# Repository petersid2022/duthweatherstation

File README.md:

# duthweatherstation

This repo contains a proposed implementation of an Integrated Automatic Weather Station, centered around the FireBeetle 2 ESP32-E microcontroller, that's based on the ESP-WROOM-32E, chosen for its ultra-low power consumption, on-board charging circuit and compatibility with a wide range of sensors. The sensor array includes a DHT11 for humidity, a BMP180 for temperature and barometric pressure, and an MQ135 for air quality monitoring.

Included in this repo:
* The ESP32 firmware
* The Go microservice that handles the data stream from the ESP32 and various SQL transactions with the MySQL database
* Our Go/TEMPL frontend app
* The final board schematic, designed using KiCad
* Various 3D renderings of the PCB generated using KiCad
* The paper that describes in detail our implementation

~~You can view the live production app on: https://duthweatherstation.azurewebsites.net/~~

## License
This project is licensed under the MIT License.

(The MIT License)
Copyright (c) 2024 Peter Sideris petersid2022@gmail.com
Permission is hereby granted, free of charge, to any person obtaining a copy of this software and associated documentation files (the 'Software'), to deal in the Software without restriction, including without limitation the rights to use, copy, modify, merge, publish, distribute, sublicense, and/or sell copies of the Software, and to permit persons to whom the Software is furnished to do so, subject to the following conditions:
The above copyright notice and this permission notice shall be included in all copies or substantial portions of the Software.
THE SOFTWARE IS PROVIDED 'AS IS', WITHOUT WARRANTY OF ANY KIND, EXPRESS OR IMPLIED, INCLUDING BUT NOT LIMITED TO THE WARRANTIES OF MERCHANTABILITY, FITNESS FOR A PARTICULAR PURPOSE AND NONINFRINGEMENT. IN NO EVENT SHALL THE AUTHORS OR COPYRIGHT HOLDERS BE LIABLE FOR ANY CLAIM, DAMAGES OR OTHER LIABILITY, WHETHER IN AN ACTION OF CONTRACT, TORT OR OTHERWISE, ARISING FROM, OUT OF OR IN CONNECTION WITH THE SOFTWARE OR THE USE OR OTHER DEALINGS IN THE SOFTWARE.

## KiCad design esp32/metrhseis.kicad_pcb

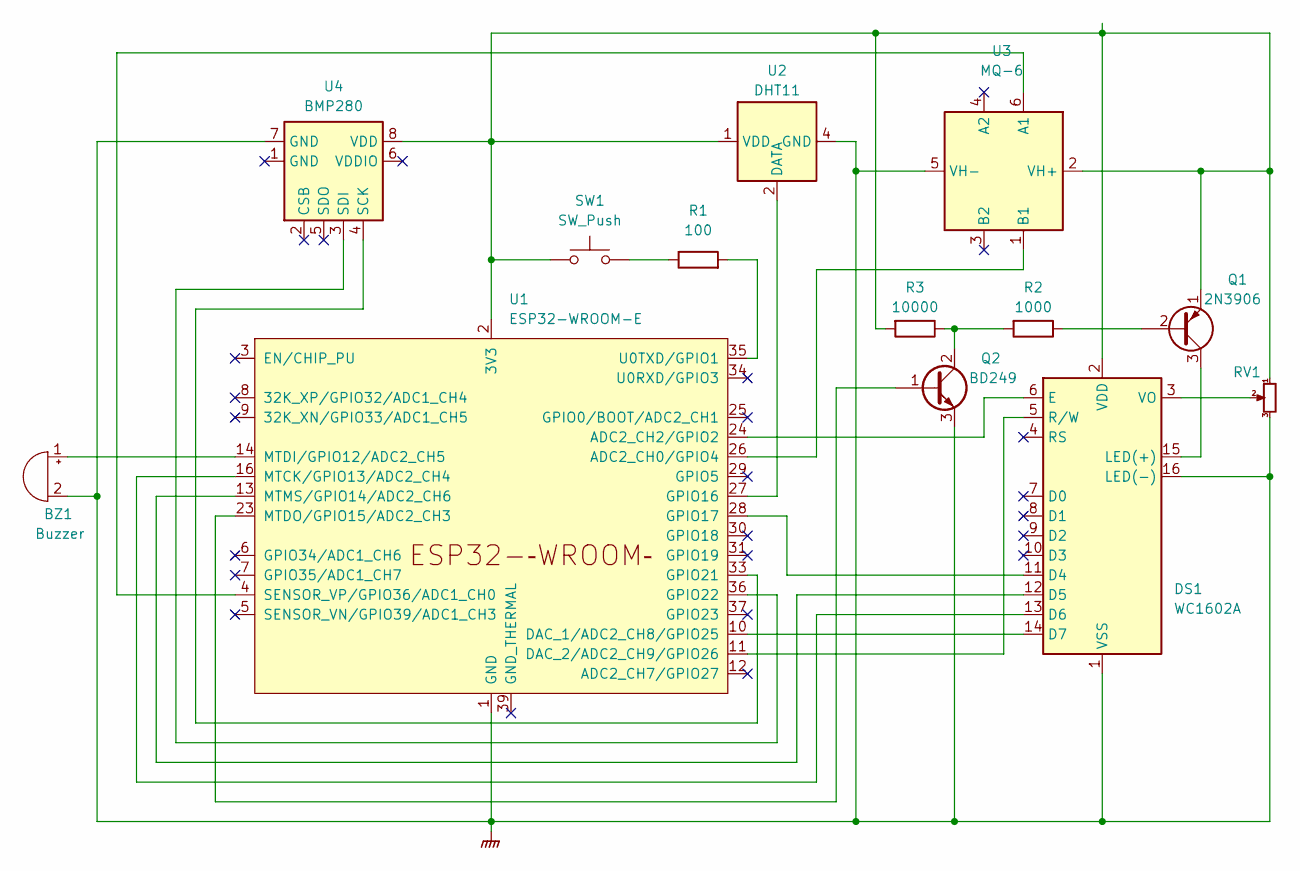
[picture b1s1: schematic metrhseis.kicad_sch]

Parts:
BZ1: Buzzer; Buzzer_12x9.5RM7.6
DS1: WC1602A
Q1: 2N3906; TO-92_Inline
Q2: BD249; SOT-1123
R1: 100; R_0603_1608Metric
R2: 1000; R_0603_1608Metric
R3: 10000; R_0603_1608Metric
RV1: R_Potentiometer_Small; Potentiometer_ACP_CA6-VSMD_Vertical
SW1: SW_Push; SW_PUSH_6mm
U1: ESP32-WROOM-E; ESP32-WROOM-32E
U2: DHT11; Aosong_DHT11_5.5x12.0_P2.54mm
U3: MQ-6
U4: BMP280; Bosch_LGA-8_2x2.5mm_P0.65mm_ClockwisePinNumbering

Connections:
GNDPWR: BZ1.2 (-), DS1.1 (VSS), DS1.16 (LED(-)), Q2.3 (E), RV1.3, U1.1 (GND), U1.15 (GND), U1.38 (GND), U2.4 (GND), U3.5 (VH-), U4.7 (GND)
unnamed: BZ1.1 (+), U1.14 (MTDI/GPIO12/ADC2_CH5)
unnamed: DS1.11 (D4), U1.28 (GPIO17)
unnamed: DS1.12 (D5), U1.13 (MTMS/GPIO14/ADC2_CH6)
unnamed: DS1.13 (D6), U1.16 (MTCK/GPIO13/ADC2_CH4)
unnamed: DS1.14 (D7), U1.10 (DAC_1/ADC2_CH8/GPIO25)
unnamed: DS1.6 (E), U1.24 (ADC2_CH2/GPIO2)
unnamed: DS1.15 (LED(+)), Q1.3 (C)
unnamed: DS1.5 (R/W), U1.11 (DAC_2/ADC2_CH9/GPIO26)
unnamed: DS1.2 (VDD), Q1.1 (E), R3.2, RV1.1, SW1.1, U1.2 (3V3), U2.1 (VDD), U3.2 (VH+), U4.8 (VDD)
unnamed: DS1.3 (VO), RV1.2
unnamed: Q1.2 (B), R2.1
unnamed: Q2.1 (B), U1.23 (MTDO/GPIO15/ADC2_CH3)
unnamed: Q2.2 (C), R2.2, R3.1
unnamed: R1.1, SW1.2
unnamed: U1.26 (ADC2_CH0/GPIO4), U3.1 (B1)
unnamed: U1.27 (GPIO16), U2.2 (DATA)
unnamed: U1.33 (GPIO21), U4.4 (SCK)
unnamed: U1.36 (GPIO22), U4.3 (SDI)
unnamed: U1.4 (SENSOR_VP/GPIO36/ADC1_CH0), U3.6 (A1)
unnamed: R1.2, U1.35 (U0TXD/GPIO1)

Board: 2 copper layers, 13 parts (0 on the bottom side), 21 nets, no tracks yet.

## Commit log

2024-05-25 duthweatherstation v1.0
2024-05-25 duthweatherstation v1.1: automatic reload and tailwind
2024-05-26 duthweatherstation v1.2 viewport magic
2024-05-26 duthweatherstation v1.3 favicon
2024-05-26 favicon: Revert changes v1.3 to v1.2
2024-05-26 Added esp32 sketch code
2024-05-26 fix: change reload interval to 5 minutes
2024-05-26 esp32: disable screen after sending data for 5 minutes
2024-05-26 feat: added last updated message
2024-05-27 Updated ESP32 code
2024-05-27 Updated gitignore
2024-05-27 Display last sensor readings
2024-05-27 Fixed reading not showing on mobile
2024-05-29 duthweatherstation v1.4 auto scale y axis and make charts prettier
2024-05-30 duthweatherstation v1.5 added brush on the charts
2024-05-30 duthweatherstation v1.6 small scaling adjustments
2024-05-30 esp32: enable immediate LCD backlight control with button press
2024-06-01 duthweatherstation v1.7 added navbar and slight appearance fixups
2024-06-02 duthweatherstation v1.8 added favicon
2024-06-06 feat: added date selection
2024-06-07 weird same day not showing measurements
2024-06-07 Cleaned up repo
2024-06-14 duthweatherstation v2 final version
2024-06-14 Updated esp32 sketch
2024-06-14 Added kicad project files
2024-06-28 Last commit
2025-01-30 Added final paper
